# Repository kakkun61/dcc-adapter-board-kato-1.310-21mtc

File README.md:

# DCC 21MTC Adapter Board for Kato 1-310

## Parts

Expected parts are:

- Side-emit LED — Bulb color
  - Quantity 2
  - https://www.led-paradise.com/phone/product/1890
- Side-emit LED — Red color
  - Quantity 4
  - https://www.led-paradise.com/phone/product/1887
- MOSFET IC ― N channel
 	- Quantity 2
 	- https://eleshop.jp/shop/g/gAA5417/
- 1/20 inch-pitch SMD pin header
  - Quantity 11
  - https://akizukidenshi.com/catalog/g/gC-10704/
- 表面実装抵抗
  - Quantity 6
  - 16×08 mm
  - 500-1k Ω

## Order to Elecrow

Rename and archive gerber files:

```
make
```

_dcc-adapter-board-kato-1.310-21mtc_elecrow.zip_ will be made and this is a file to submit to Elecrow.

Order parameters are:

Parameter | Argument
---|---
Layer | 2
Dimensions | 60×16 mm
Thickness | 1.0 mm
Color | Black
Surface Finish | HASL
Castellated Hole | No
Copper Weight | 1 oz

## License

[CC BY 4.0](https://creativecommons.org/licenses/by/4.0/deed) 岡本和樹

[Open Source Hardware](https://www.oshwa.org/)

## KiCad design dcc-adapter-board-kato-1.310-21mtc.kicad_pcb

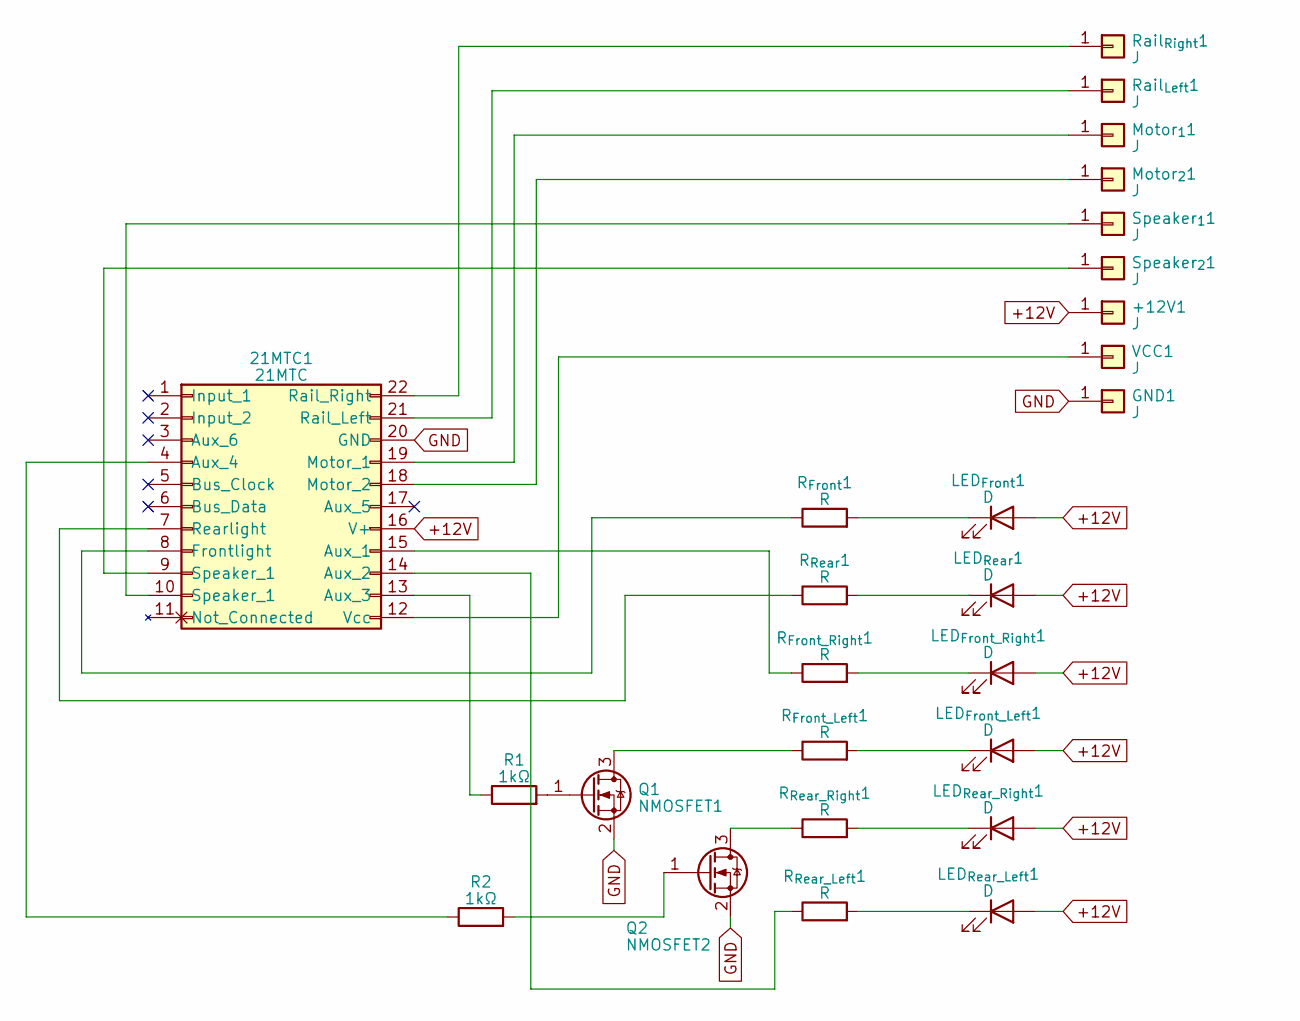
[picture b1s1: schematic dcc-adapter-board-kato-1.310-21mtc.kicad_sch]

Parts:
21MTC1: 21MTC
+12V1: J; SolderWirePad_1x01_SMD_1x2mm
GND1: J; SolderWirePad_1x01_SMD_1x2mm
LED_{Front_Left}1: D; LED_Side_Emitting_335
LED_{Front_Right}1: D; LED_Side_Emitting_335
LED_{Front}1: D; LED_Side_Emitting_335
LED_{Rear_Left}1: D; LED_Side_Emitting_335
LED_{Rear_Right}1: D; LED_Side_Emitting_335
LED_{Rear}1: D; LED_Side_Emitting_335
Motor_{1}1, Motor_{2}1: J; SolderWirePad_1x01_SMD_1x2mm
Q1: NMOSFET1; SOT-23
Q2: NMOSFET2; SOT-23
R1, R2: 1kΩ; R_0603_1608Metric_Pad0.98x0.95mm_HandSolder
R_{Front_Left}1: R; R_0603_1608Metric_Pad0.98x0.95mm_HandSolder
R_{Front_Right}1: R; R_0603_1608Metric_Pad0.98x0.95mm_HandSolder
R_{Front}1: R; R_0603_1608Metric_Pad0.98x0.95mm_HandSolder
R_{Rear_Left}1: R; R_0603_1608Metric_Pad0.98x0.95mm_HandSolder
R_{Rear_Right}1: R; R_0603_1608Metric_Pad0.98x0.95mm_HandSolder
R_{Rear}1: R; R_0603_1608Metric_Pad0.98x0.95mm_HandSolder
Rail_{Left}1: J; SolderWire-1.5sqmm_1x01_D1.7mm_OD3.9mm
Rail_{Right}1: J; SolderWire-1.5sqmm_1x01_D1.7mm_OD3.9mm
Speaker_{1}1, Speaker_{2}1: J; SolderWirePad_1x01_SMD_1x2mm
VCC1: J; SolderWirePad_1x01_SMD_1x2mm

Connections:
+12V: 21MTC1.16 (V+), +12V1.1, LED_{Front_Left}1.2 (A), LED_{Front_Right}1.2 (A), LED_{Front}1.2 (A), LED_{Rear_Left}1.2 (A), LED_{Rear_Right}1.2 (A), LED_{Rear}1.2 (A)
GND: 21MTC1.20 (GND), GND1.1, Q1.2 (S), Q2.2 (S)
unnamed: 21MTC1.15 (Aux_1), R_{Front_Right}1.1
unnamed: 21MTC1.14 (Aux_2), R_{Rear_Left}1.1
unnamed: 21MTC1.13 (Aux_3), R1.1
unnamed: 21MTC1.4 (Aux_4), R2.1
unnamed: 21MTC1.8 (Frontlight), R_{Front}1.1
unnamed: 21MTC1.19 (Motor_1), Motor_{1}1.1
unnamed: 21MTC1.18 (Motor_2), Motor_{2}1.1
unnamed: 21MTC1.21 (Rail_Left), Rail_{Left}1.1
unnamed: 21MTC1.22 (Rail_Right), Rail_{Right}1.1
unnamed: 21MTC1.7 (Rearlight), R_{Rear}1.1
unnamed: 21MTC1.12 (Vcc), VCC1.1
unnamed: LED_{Front_Left}1.1 (K), R_{Front_Left}1.2
unnamed: LED_{Front_Right}1.1 (K), R_{Front_Right}1.2
unnamed: LED_{Front}1.1 (K), R_{Front}1.2
unnamed: LED_{Rear_Left}1.1 (K), R_{Rear_Left}1.2
unnamed: LED_{Rear_Right}1.1 (K), R_{Rear_Right}1.2
unnamed: LED_{Rear}1.1 (K), R_{Rear}1.2
unnamed: Q1.3 (D), R_{Front_Left}1.1
unnamed: Q1.1 (G), R1.2
unnamed: Q2.3 (D), R_{Rear_Right}1.1
unnamed: Q2.1 (G), R2.2
unnamed: 21MTC1.10 (Speaker_1), Speaker_{1}1.1
unnamed: 21MTC1.9 (Speaker_1), Speaker_{2}1.1

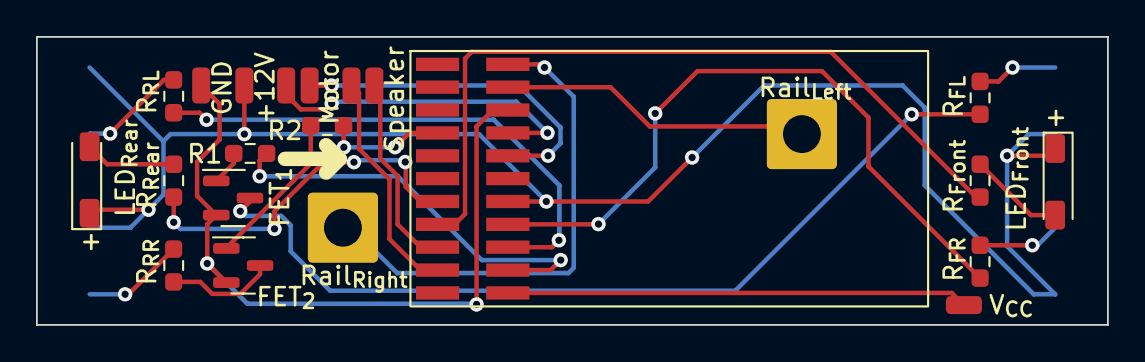
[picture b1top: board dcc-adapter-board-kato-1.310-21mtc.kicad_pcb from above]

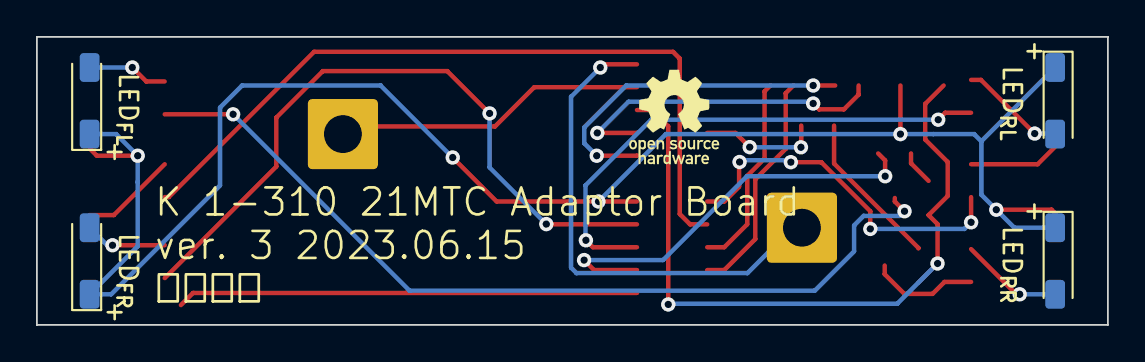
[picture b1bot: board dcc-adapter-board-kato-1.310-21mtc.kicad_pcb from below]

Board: 2 copper layers, 59.5 x 16.0 mm, 27 parts (5 on the bottom side), 25 nets.

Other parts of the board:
G1: LOGO

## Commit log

2023-04-19 init
2023-04-20 gerber
2023-04-28 KiCad の出力するファイル名が …-F_SilkS.ghr から …-F_Silkscreen.gbr に変わったんか
2023-04-28 試作1号 フィードバック
    ねじ穴位置修正
    プラス表記
    銅層の文字をシルクスクリーンに移動
2023-05-17 改修
    • 21MTC のピン配置がまちがっていた
    • アライブキャパシター用端子をなくした
    • +12V・GND パッドを使うようにする
2023-05-17 Makefile
2023-05-17 clean and archive task
2023-05-17 update gerbers
2023-05-17 README
2023-05-17 refer a lib by submodule
2023-05-28 v2 フィードバック
    • MOSFET のゲートの前段に抵抗を追加
    • ねじ穴の位置を 0.5mm 外側に移動
2023-06-13 シルクスクリーン配置変更
2023-06-13 create-gerber.py とそれで生成されたファイル
    時刻以外の差分はよく分からん
2023-06-13 gerber ファイルは管理下外に
2023-06-13 make から呼びだせるように
2023-06-16 G code with inches
